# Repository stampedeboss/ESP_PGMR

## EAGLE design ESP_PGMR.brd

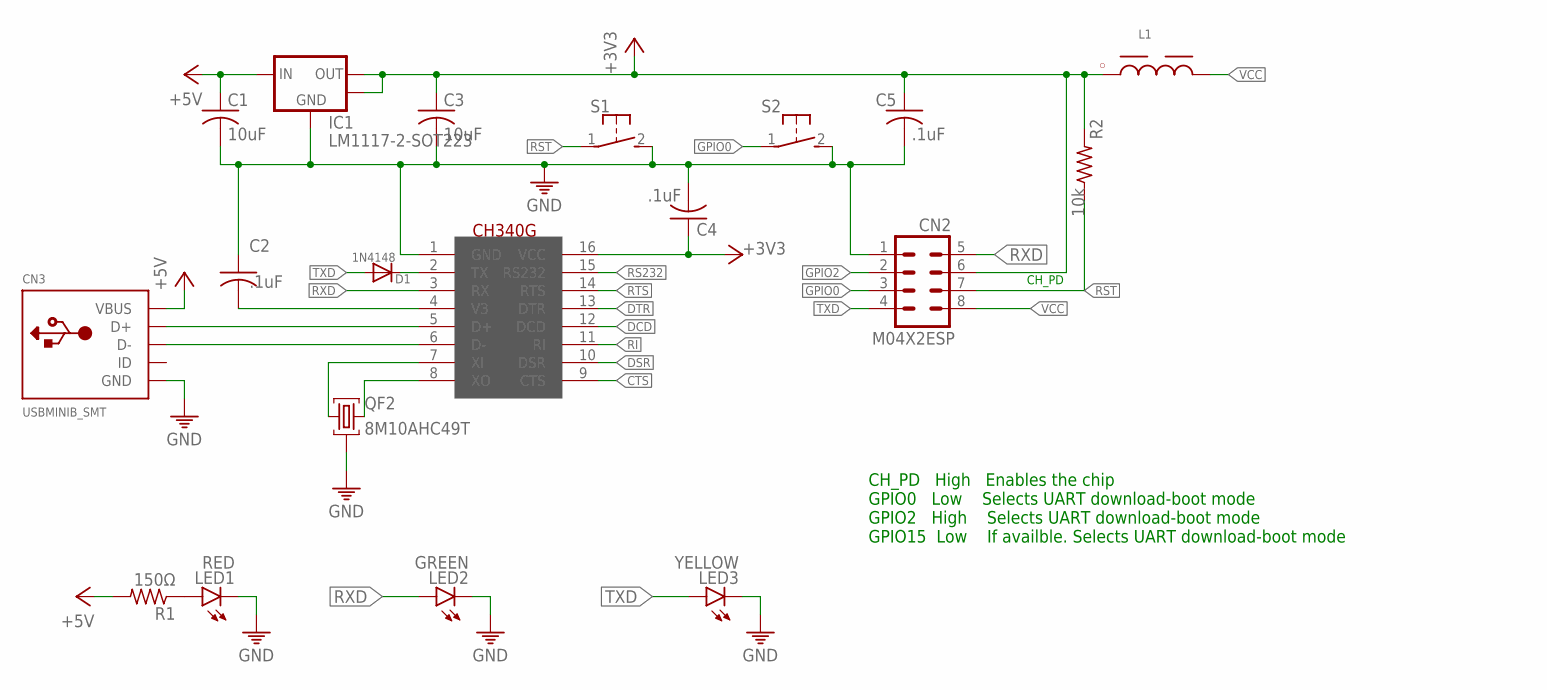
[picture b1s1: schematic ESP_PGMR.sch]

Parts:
C1, C3: 10uF; C0805
C2, C4, C5: .1uF; C0805
CN2: M04X2ESP; 2X04-ESP
CN3: USBMINIB_SMT; USB_MINI_B
D1: 1N4148; SOD-123
IC1: LM1117-2-SOT223; SOT-223-3
IC2: CH340G; SOIC16
L1: WE-CBA_0805_782851102_WB/HS; WE-CBA_0805(W=3)
LED1: RED; CHIPLED_1206
LED2: GREEN; CHIPLED_1206
LED3: YELLOW; CHIPLED_1206
QF2: 8M10AHC49T; HC49U
R1: 150Ω; M0805
R2: 10k; R0805
S1, S2: MOMENTARY-SWITCH-SPST-PTH-6.0X6.0-5MM; TACTILE_SWITCH_PTH_6.0X6.0-5MM

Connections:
+3V3: C3.1, C4.1, C5.1, CN2.6, IC1.2 (VOUT), IC1.4 (HEATSINK), IC2.16 (VCC), L1.1, R2.2
+5V: C1.1, CN3.VBUS, IC1.3 (VIN), R1.2
CTS: IC2.9 (CTS)
D+: CN3.D+, IC2.5 (D+)
D-: CN3.D-, IC2.6 (D-)
DCD: IC2.12 (DCD)
DSR: IC2.10 (DSR)
DTR: IC2.13 (DTR)
GND: C1.2, C2.1, C3.2, C4.2, C5.2, CN2.1, CN3.GND, CN3.GND1 (GND), CN3.GND2 (GND), CN3.GND3 (GND), CN3.GND4 (GND), IC1.1 (GND), IC2.1 (GND), LED1.C, LED2.C, LED3.C, QF2.2, S1.2 (S), S2.2 (S)
GPIO0: CN2.3, S2.1
GPIO2: CN2.2
unnamed: IC2.7 (XI), QF2.1
unnamed: IC2.8 (XO), QF2.3
unnamed: LED1.A, R1.1
unnamed: C2.2, IC2.4 (V3)
RI: IC2.11 (RI)
RS232: IC2.15 (RS232)
RST: CN2.7, R2.1, S1.1
RTS: IC2.14 (RTS)
RXD: CN2.5, IC2.3 (RX), LED2.A
TX: D1.C, IC2.2 (TX)
TXD: CN2.4, D1.A, LED3.A
VCC: CN2.8, L1.2

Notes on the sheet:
CH_PD High Enables the chip GPIO0 Low Selects UART download-boot mode GPIO2 High Selects UART download-boot mode GPIO15 Low If availble. Selects UART download-boot mode
CH_PD

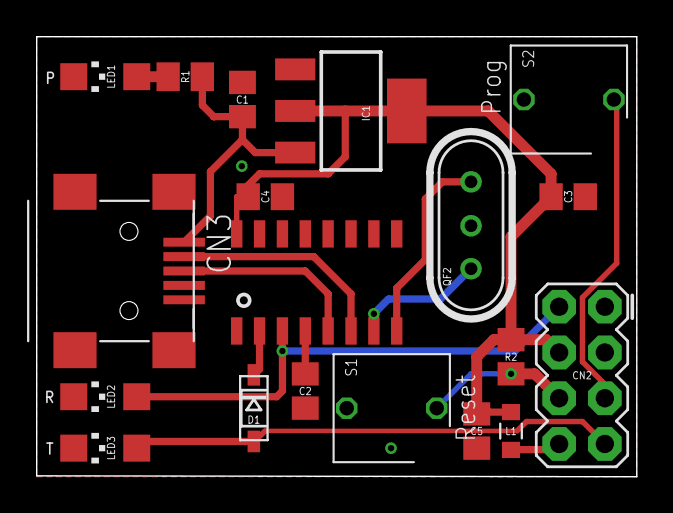
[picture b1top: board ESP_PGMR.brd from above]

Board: 2 copper layers, 33.3 x 24.4 mm, 19 parts (0 on the bottom side), 15 nets.

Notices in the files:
parts and their libraries:
Wurth_Elektronik_Passive_rev19b: Copyright: Würth Elektronik
